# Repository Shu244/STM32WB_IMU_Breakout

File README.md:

## Overview

This repo contains a 4 layer PCB (signal - ground - ground - power) that contains BLE, IMU, and battery capabilities using
a STM32WB MCU.

This project extends Phil Lab's two part tutorial:

1) Schematic: https://www.youtube.com/watch?v=nkHFoxe0mrU&t=6654s
2) PCB: https://www.youtube.com/watch?v=PlXd3lLZ4vc

This project includes the following additions to the tutorial:

1) Charging IC and peripherals to support LiPo battery (IC was selected to support power path i.e. provide power while charging)
2) ST IMU chip

## Results

### PCB Board

Top View:

Bottom View:

### PCB Routing

Top View:

Bottom View:

### Schematic

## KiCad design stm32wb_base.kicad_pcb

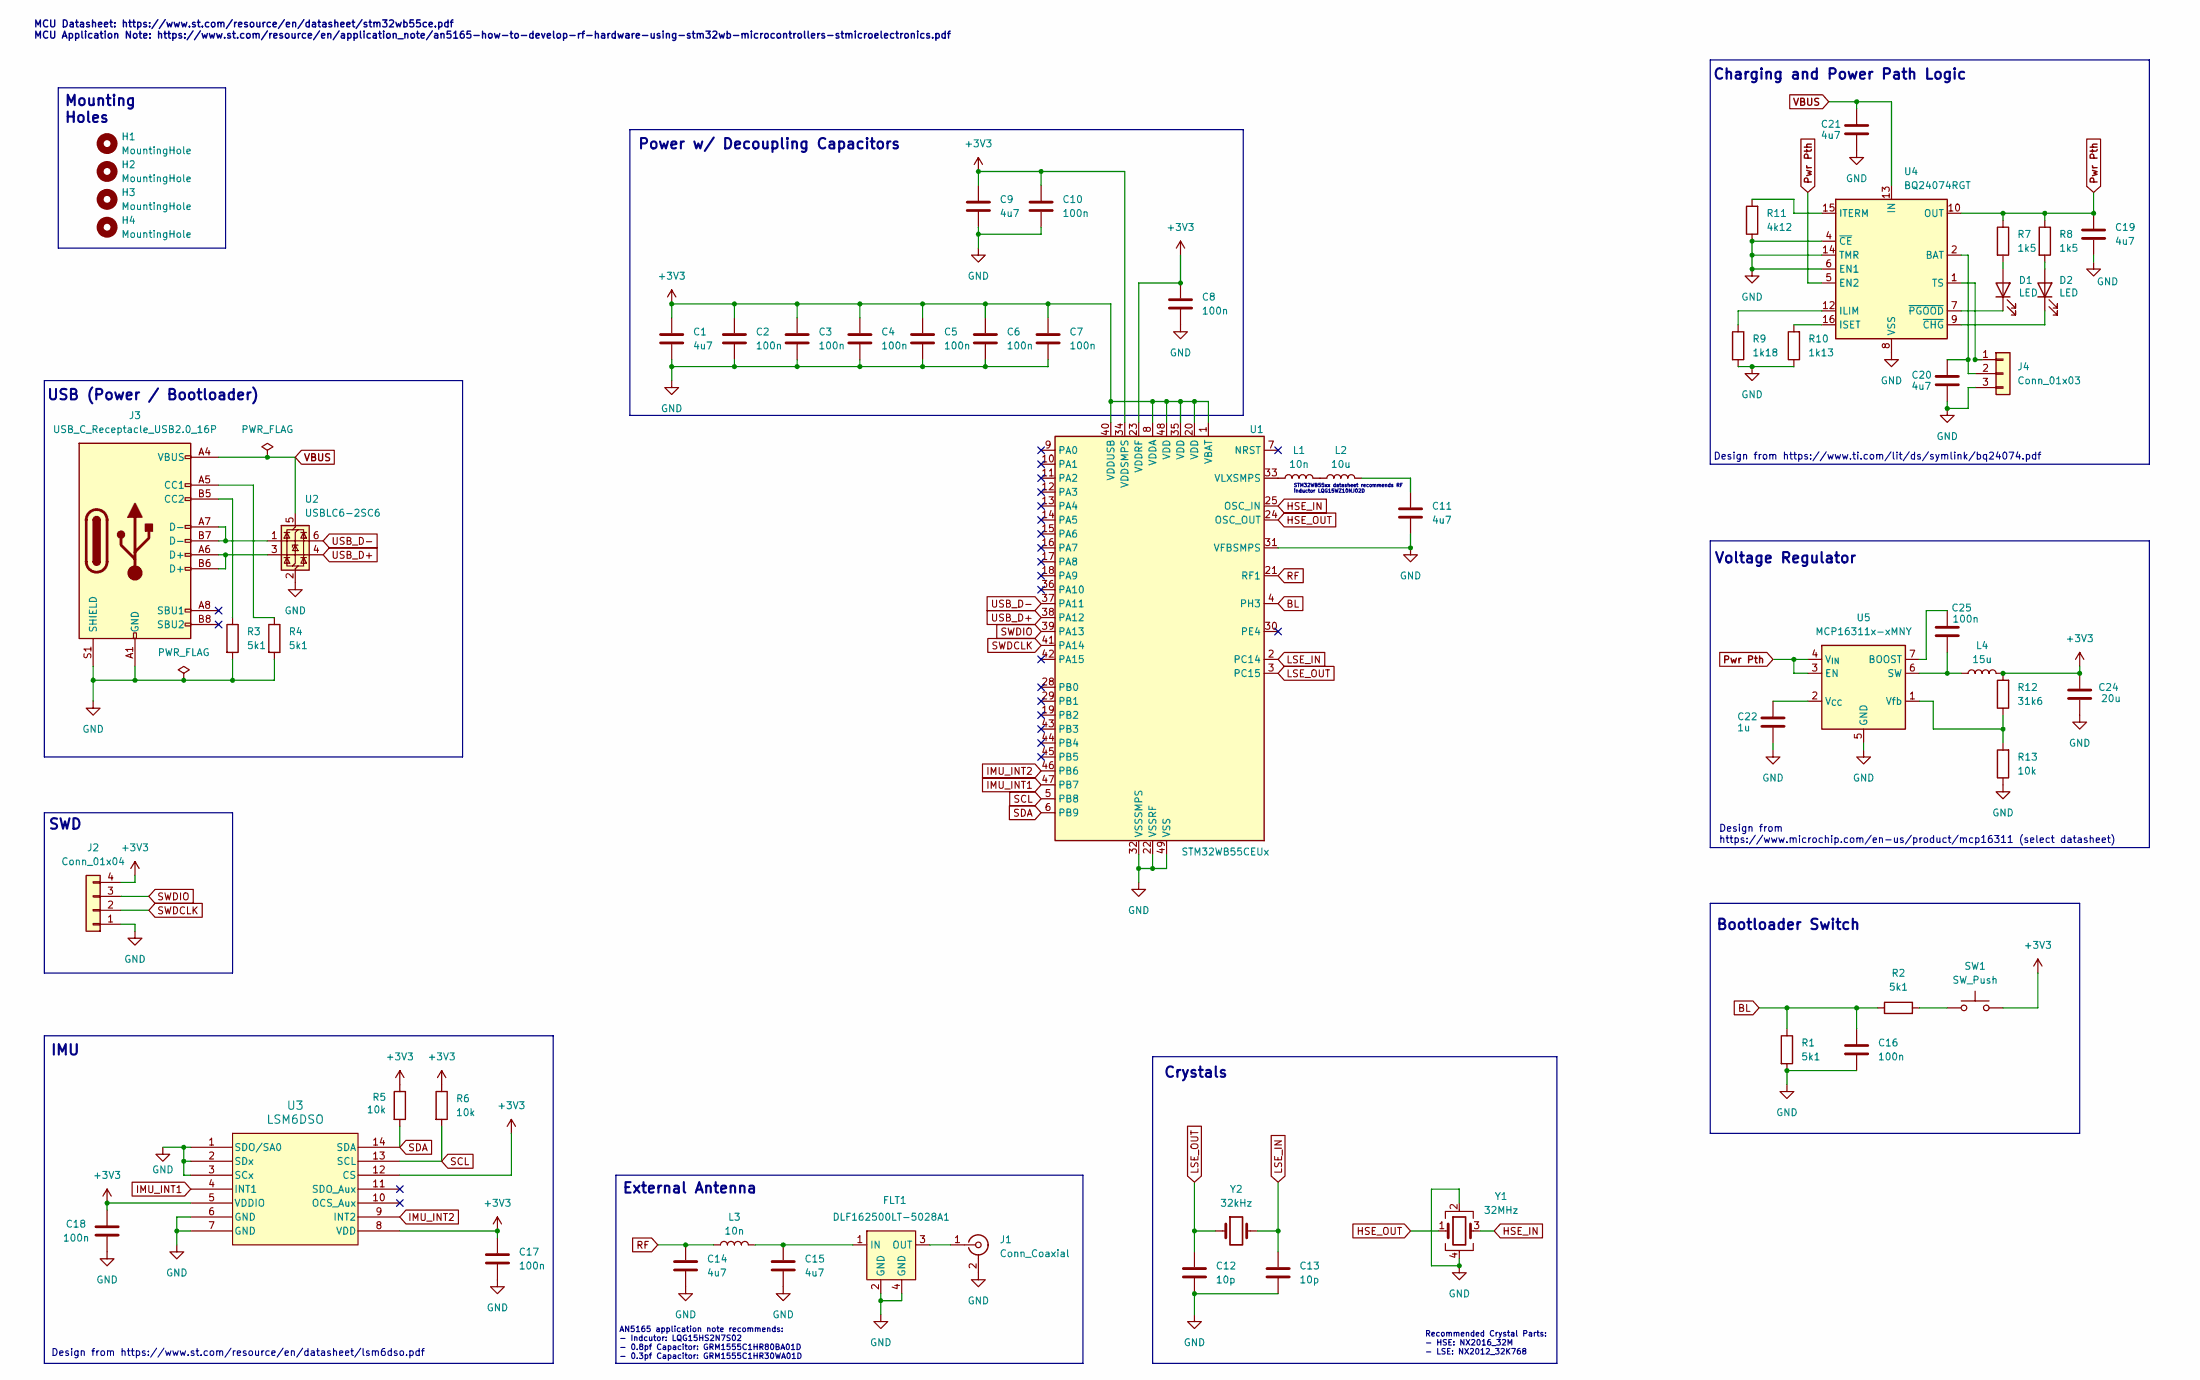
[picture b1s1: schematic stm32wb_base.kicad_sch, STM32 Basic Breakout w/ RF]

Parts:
C1, C9, C11, C14, C15, C19, C20, C21: 4u7; C_0402_1005Metric
C2, C3, C4, C5, C6, C7, C8, C10, C16, C17, C18, C25: 100n; C_0402_1005Metric
C12, C13: 10p; C_0402_1005Metric
C22: 1u; C_0402_1005Metric
C24: 20u; C_0402_1005Metric
D1, D2: LED; LED_0402_1005Metric
FLT1: DLF162500LT-5028A1
H1, H2, H3, H4: MountingHole; MountingHole_2.1mm
J1: Conn_Coaxial; U.FL_Hirose_U.FL-R-SMT-1_Vertical
J2: Conn_01x04; PinHeader_1x04_P2.54mm_Vertical
J3: USB_C_Receptacle_USB2.0_16P; USB_C_Receptacle_GCT_USB4105-xx-A_16P_TopMnt_Horizontal
J4: Conn_01x03; JST_PH_B3B-PH-K_1x03_P2.00mm_Vertical
L1, L3: 10n; L_0402_1005Metric
L2: 10u; L_0805_2012Metric
L4: 15u; L_0402_1005Metric
R1, R2, R3, R4: 5k1; R_0402_1005Metric
R5, R6, R13: 10k; R_0402_1005Metric
R7, R8: 1k5; R_0402_1005Metric
R9: 1k18; R_0402_1005Metric
R10: 1k13; R_0402_1005Metric
R11: 4k12; R_0402_1005Metric
R12: 31k6; R_0402_1005Metric
SW1: SW_Push; SW_SPST_CK_RS282G05A3
U1: STM32WB55CEUx; QFN-48-1EP_7x7mm_P0.5mm_EP5.6x5.6mm
U2: USBLC6-2SC6; SOT-23-6
U3: LSM6DSO
U4: BQ24074RGT; VQFN-16-1EP_3x3mm_P0.5mm_EP1.6x1.6mm
U5: MCP16311x-xMNY; DFN-8-1EP_3x2mm_P0.5mm_EP1.75x1.45mm
Y1: 32MHz; Crystal_SMD_2016-4Pin_2.0x1.6mm
Y2: 32kHz; Crystal_SMD_2012-2Pin_2.0x1.2mm

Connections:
+3V3: C1.1, C2.1, C3.1, C4.1, C5.1, C6.1, C7.1, C8.1, C9.1, C10.1, C17.1, C18.1, C24.1, J2.4, L4.2, R5.1, R6.1, R12.2, SW1.2, U1.1 (VBAT), U1.8 (VDDA), U1.20 (VDD), U1.23 (VDDRF), U1.34 (VDDSMPS), U1.35 (VDD), U1.40 (VDDUSB), U1.48 (VDD), U3.5 (VDDIO), U3.8 (VDD), U3.12 (CS)
BL: C16.1, R1.1, R2.1, U1.4 (PH3)
GND: C1.2, C2.2, C3.2, C4.2, C5.2, C6.2, C7.2, C8.2, C9.2, C10.2, C11.2, C12.2, C13.2, C14.2, C15.2, C16.2, C17.2, C18.2, C19.2, C20.2, C21.2, C22.2, C24.2, FLT1.2 (GND), FLT1.4 (GND), J1.2 (Ext), J2.1, J3.A1 (GND), J3.A12 (GND), J3.B1 (GND), J3.B12 (GND), J3.S1 (SHIELD), J4.3, R1.2, R3.2, R4.2, R9.2, R10.1, R11.1, R13.1, U1.22 (VSSRF), U1.31 (VFBSMPS), U1.32 (VSSSMPS), U1.49 (VSS), U2.2 (GND), U3.1 (SDO/SA0), U3.2 (SDx), U3.3 (SCx), U3.6 (GND), U3.7 (GND), U4.4 (~CE), U4.6 (EN1), U4.8 (VSS), U4.14 (TMR), U4.17 (VSS), U5.5 (GND), U5.8 (GND), U5.9 (GND), Y1.2, Y1.4
HSE_IN: U1.25 (OSC_IN), Y1.3
HSE_OUT: U1.24 (OSC_OUT), Y1.1
IMU_INT1: U1.47 (PB7), U3.4 (INT1)
IMU_INT2: U1.46 (PB6), U3.9 (INT2)
LSE_IN: C13.1, U1.2 (PC14), Y2.2
LSE_OUT: C12.1, U1.3 (PC15), Y2.1
unnamed: C11.1, L2.2
unnamed: D1.2 (A), R7.2
unnamed: D1.1 (K), U4.7 (~PGOOD)
unnamed: D2.2 (A), R8.2
unnamed: D2.1 (K), U4.9 (~CHG)
unnamed: C15.1, FLT1.1 (IN), L3.2
unnamed: FLT1.3 (OUT), J1.1 (In)
unnamed: J3.A5 (CC1), R4.1
unnamed: J3.B5 (CC2), R3.1
unnamed: J3.A6 (D+), J3.B6 (D+), U2.3 (I/O2)
unnamed: J3.A7 (D-), J3.B7 (D-), U2.1 (I/O1)
unnamed: J4.1, U4.1 (TS)
unnamed: C20.1, J4.2, U4.2 (BAT), U4.3 (BAT)
unnamed: L1.2, L2.1
unnamed: R2.2, SW1.1
unnamed: L1.1, U1.33 (VLXSMPS)
unnamed: R9.1, U4.12 (ILIM)
unnamed: R10.2, U4.16 (ISET)
unnamed: R11.2, U4.15 (ITERM)
unnamed: C25.2, U5.7 (BOOST)
unnamed: C25.1, L4.1, U5.6 (SW)
unnamed: C22.1, U5.2 (V_{CC})
unnamed: R12.1, R13.2, U5.1 (Vfb)
Pwr Pth: C19.1, R7.1, R8.1, U4.5 (EN2), U4.10 (OUT), U4.11 (OUT), U5.3 (EN), U5.4 (V_{IN})
RF: C14.1, L3.1, U1.21 (RF1)
SCL: R6.2, U1.5 (PB8), U3.13 (SCL)
SDA: R5.2, U1.6 (PB9), U3.14 (SDA)
SWDCLK: J2.2, U1.41 (PA14)
SWDIO: J2.3, U1.39 (PA13)
USB_D+: U1.38 (PA12), U2.4 (I/O2)
USB_D-: U1.37 (PA11), U2.6 (I/O1)
VBUS: C21.1, J3.A4 (VBUS), J3.A9 (VBUS), J3.B4 (VBUS), J3.B9 (VBUS), U2.5 (VBUS), U4.13 (IN)

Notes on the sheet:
Design from https://www.microchip.com/en-us/product/mcp16311 (select datasheet)
Charging and Power Path Logic
SWD
IMU
USB (Power / Bootloader)
Design from https://www.st.com/resource/en/datasheet/lsm6dso.pdf
Mounting Holes
MCU Datasheet: https://www.st.com/resource/en/datasheet/stm32wb55ce.pdf MCU Application Note: https://www.st.com/resource/en/application_note/an5165-how-to-develop-rf-hardware-using-stm32wb-microcontrollers-stmicroelectronics.pdf
Bootloader Switch
Power w/ Decoupling Capacitors
Design from https://www.ti.com/lit/ds/symlink/bq24074.pdf
STM32WB55xx datasheet recommends RF inductor LQG15WZ10NJ02D
Voltage Regulator
Recommended Crystal Parts: - HSE: NX2016_32M - LSE: NX2012_32K768
External Antenna
Crystals
AN5165 application note recommends: - Indcutor: LQG15HS2N7S02 - 0.8pf Capacitor: GRM1555C1HR80BA01D - 0.3pf Capacitor: GRM1555C1HR30WA01D

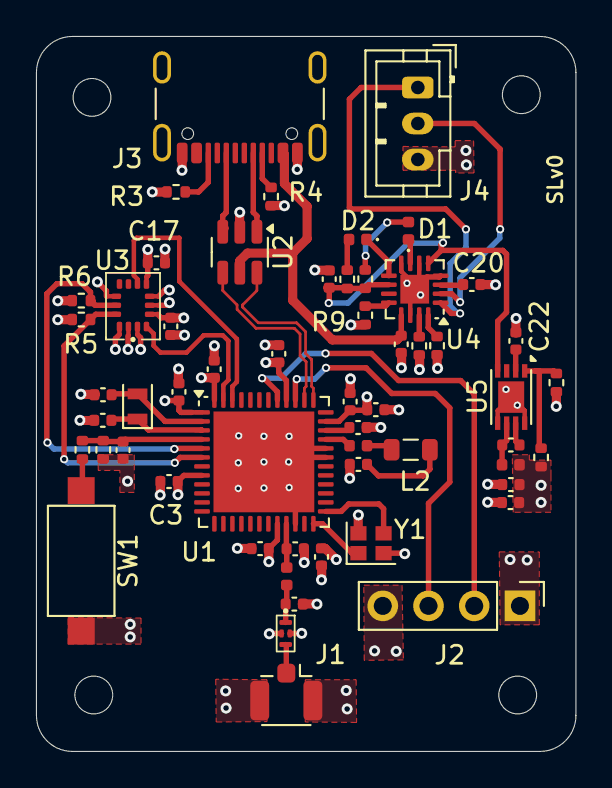
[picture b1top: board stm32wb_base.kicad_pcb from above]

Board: 4 copper layers, 30.0 x 39.7 mm, 60 parts (0 on the bottom side), 41 nets.

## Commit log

2024-11-22 STM32WB breakout board with charger and IMU
2024-11-22 Added readme and manufactoring files
2024-11-22 added bottom 3d view
2024-11-22 update schematic image
2024-11-22 update company and version
2024-11-26 updated schematic image
2024-11-27 updated vias on thermal pads
